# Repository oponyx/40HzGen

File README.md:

:warning: **warning:This device will flash/strobe the light!  Don't use it next to individuals with epilepsy!** :warning:

:warning: **The research has not been tested and has not been proven to work on humans! Use it at your own risk!** :warning:

#
# 40HzGen
An advanced [ESP8266](https://en.wikipedia.org/wiki/ESP8266) based device used to drive a 40Hz (programmable) flashing led light for brain stimulation and non invasive Alzheimer Gamma Light Therapy.

https://www.webmd.com/brain/what-to-know-about-gamma-brain-waves

http://news.mit.edu/2016/visual-stimulation-treatment-alzheimer-1207

https://picower.mit.edu/innovations-inventions/genus

### Features:
  * Complete configuration and control through web pages
  * Programmable Light On-Time, flickering Frequence and Brightness 
  * WIFI Station and AP mode
#

# Prototype board

### Hardware notes:
 * Board designed to be fitted with 'Wemos D1 mini' or 'ESP12F' modules
 * Optional OLED SS1306 Display 
 * Power to logic from AC main (populating PS1 with a HLK-PM01 module) or external 5V
 * External Input for Light Power 
 * ESP01 version (in progress)

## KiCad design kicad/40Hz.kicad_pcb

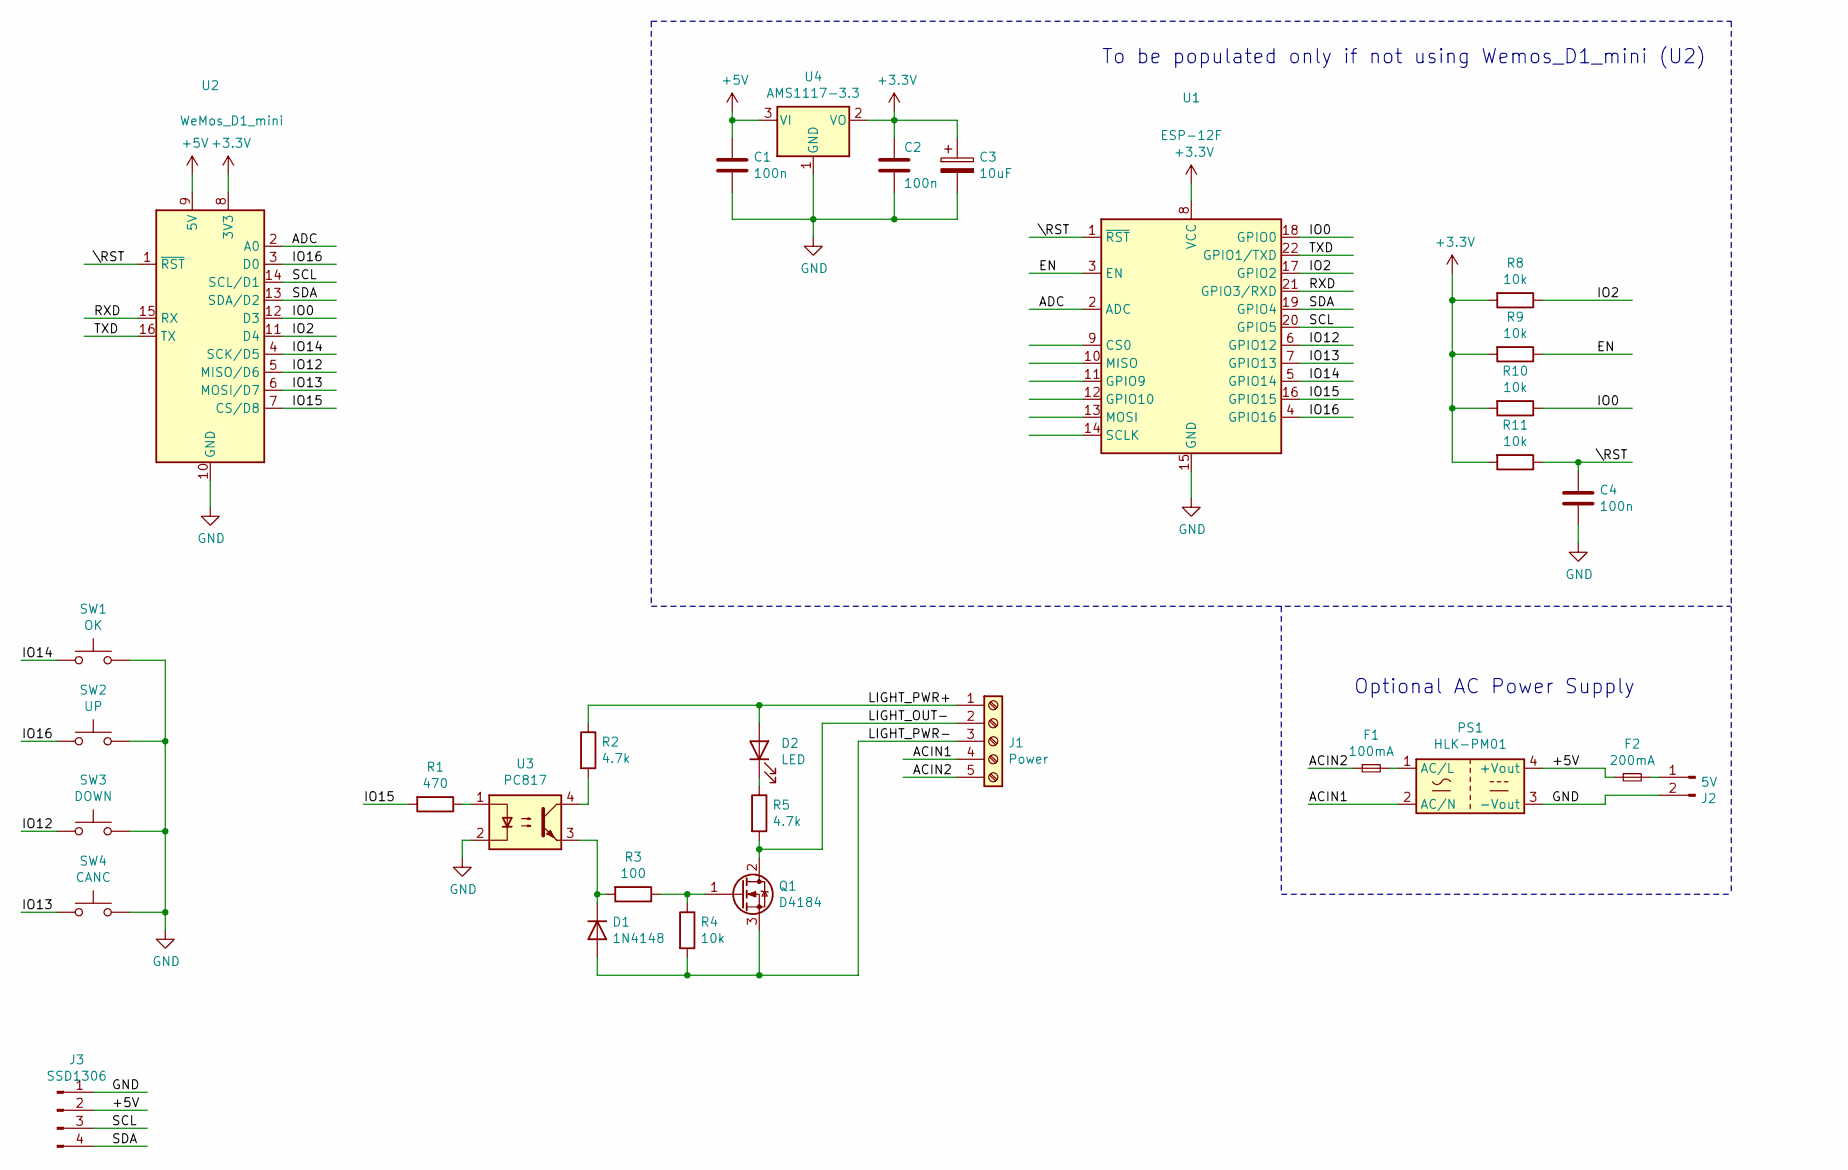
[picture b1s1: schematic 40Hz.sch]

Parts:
C1, C2, C4: 100n; C_1206_3216Metric
C3: 10uF; CP_Radial_D5.0mm_P2.50mm
D1: 1N4148; D_SOD-123
D2: LED; LED_1206_3216Metric_Pad1.42x1.75mm_HandSolder
F1: 100mA; Fuse_1206_3216Metric
F2: 200mA; Fuse_1206_3216Metric
J1: Power; TerminalBlock_Phoenix_MKDS-3-5-5.08_1x05_P5.08mm_Horizontal
J2: 5V; TerminalBlock_Phoenix_MKDS-3-2-5.08_1x02_P5.08mm_Horizontal
J3: SSD1306; JST_EH_B4B-EH-A_1x04_P2.50mm_Vertical
PS1: HLK-PM01; Converter_ACDC_HiLink_HLK-PMxx
Q1: D4184; TO-252-2
R1: 470; R_1206_3216Metric
R2, R5: 4.7k; R_1206_3216Metric
R3: 100; R_1206_3216Metric
R4, R8, R9, R10, R11: 10k; R_1206_3216Metric
SW1: OK; SW_PUSH_6mm_H5mm
SW2: UP; SW_PUSH_6mm_H5mm
SW3: DOWN; SW_PUSH_6mm_H5mm
SW4: CANC; SW_PUSH_6mm_H5mm
U1: ESP-12F; ESP-12E
U2: WeMos_D1_mini; WEMOS_D1_mini_light
U3: PC817; SOP-4_3.8x4.1mm_P2.54mm
U4: AMS1117-3.3; SOT-223-3_TabPin2

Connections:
+3V3: C2.1, C3.1, R8.2, R9.2, R10.2, R11.2, U1.8 (VCC), U2.8 (3V3), U4.2 (VO)
+5V: C1.1, F2.1, J3.2, PS1.4 (+Vout), U2.9 (5V), U4.3 (VI)
/ACIN1: J1.4, PS1.2 (AC/N)
/ACIN2: F1.1, J1.5
/ADC: U1.2 (ADC), U2.2 (A0)
/EN: R9.1, U1.3 (EN)
/IO0: R10.1, U1.18 (GPIO0), U2.12 (D3)
/IO2: R8.1, U1.17 (GPIO2), U2.11 (D4)
/IO12: SW3.1, U1.6 (GPIO12), U2.5 (MISO/D6)
/IO13: SW4.1, U1.7 (GPIO13), U2.6 (MOSI/D7)
/IO14: SW1.1, U1.5 (GPIO14), U2.4 (SCK/D5)
/IO15: R1.2, U1.16 (GPIO15), U2.7 (CS/D8)
/IO16: SW2.1, U1.4 (GPIO16), U2.3 (D0)
/LIGHT_OUT-: J1.2, Q1.2 (D), R5.2
/LIGHT_PWR+: D2.2 (A), J1.1, R2.1
/LIGHT_PWR-: D1.2 (A), J1.3, Q1.3 (S), R4.2
/RXD: U1.21 (GPIO3/RXD), U2.15 (RX)
/SCL: J3.3, U1.20 (GPIO5), U2.14 (SCL/D1)
/SDA: J3.4, U1.19 (GPIO4), U2.13 (SDA/D2)
/TXD: U1.22 (GPIO1/TXD), U2.16 (TX)
/\RST: C4.1, R11.1, U1.1 (~RST), U2.1 (~RST)
GND: C1.2, C2.2, C3.2, C4.2, J2.2, J3.1, PS1.3 (-Vout), SW1.2, SW2.2, SW3.2, SW4.2, U1.15 (GND), U2.10 (GND), U3.2, U4.1 (GND)
unnamed: D1.1 (K), R3.2, U3.3
unnamed: D2.1 (K), R5.1
unnamed: F1.2, PS1.1 (AC/L)
unnamed: F2.2, J2.1
unnamed: Q1.1 (G), R3.1, R4.1
unnamed: R1.1, U3.1
unnamed: R2.2, U3.4

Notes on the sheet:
To be populated only if not using Wemos_D1_mini (U2)
Optional AC Power Supply

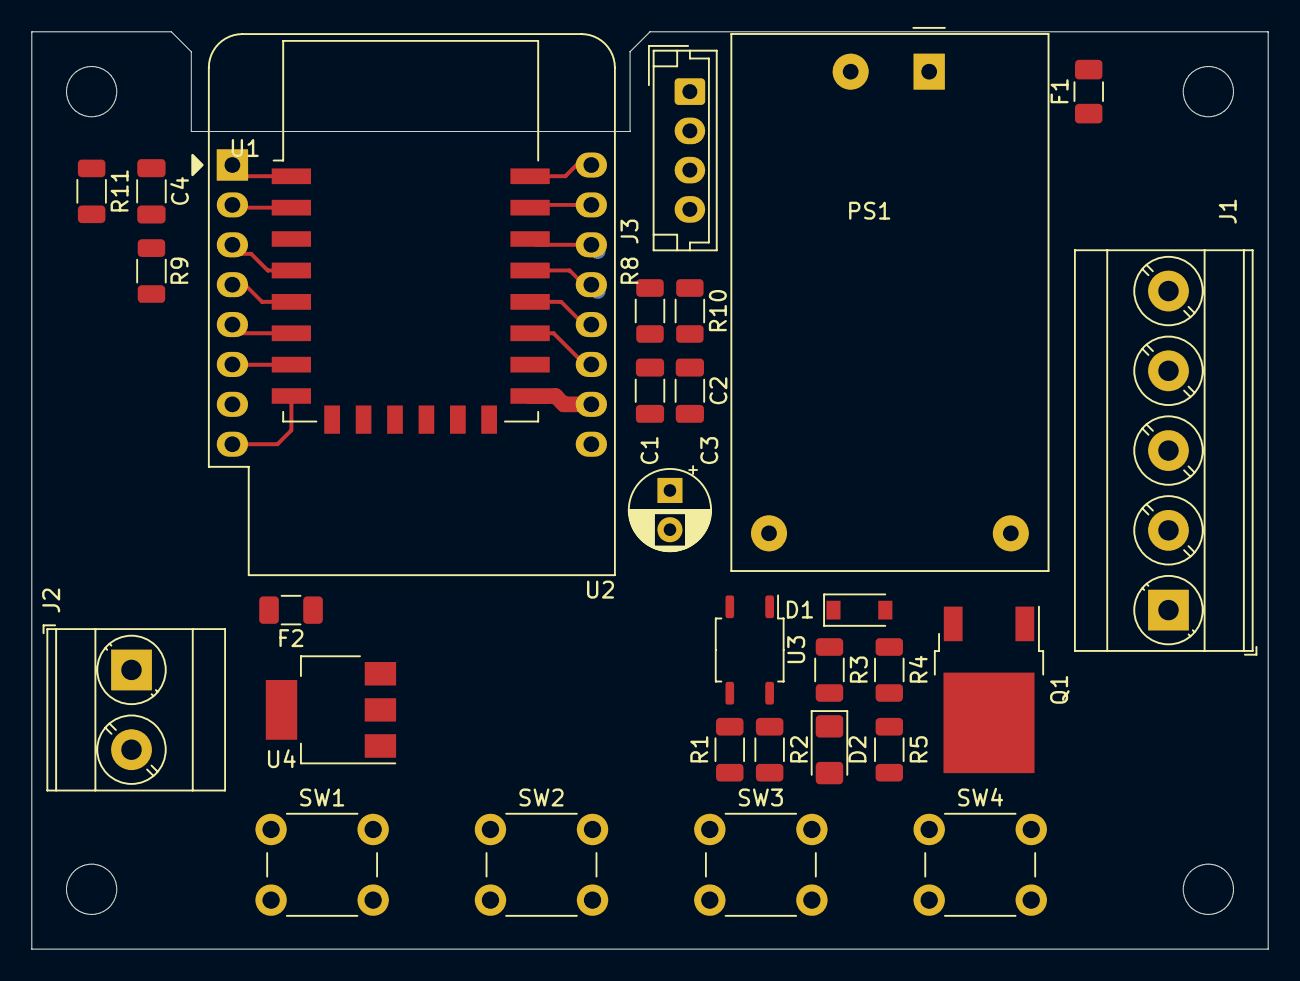
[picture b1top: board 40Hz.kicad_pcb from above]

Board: 2 copper layers, 78.7 x 58.4 mm, 30 parts (0 on the bottom side), 29 nets.

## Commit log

2022-02-04 reorg
2022-02-18 test release
2022-02-24 deleted html files
2022-02-24 Corrected rebooting page send
2022-02-24 added redirect to rebootin page
2022-02-24 Minimal functions documentation
2022-02-24 Schematics update
2022-02-25 Add CRC Check on Settings
2022-02-26 Corrected CRC
2022-02-26 Fuse added
2022-02-26 Schematic update
2022-02-27 several corrections
2022-02-27 Added slider
2022-03-03 Button alpha
2022-03-03 test
2022-03-08 New Buttons, no ISR
2022-03-12 increase speed
2022-03-19 Release
2022-03-19 Create LICENSE
2022-03-19 added license notes
2022-03-21 Minimal ESP01 support
2022-04-05 Add Firmware update page
2022-04-20 Bug correction
2022-09-26 v0.0.1
2022-09-27 Corrections for env d1_mini (no LCD)
2023-05-09 Preliminary ESP32 Support
